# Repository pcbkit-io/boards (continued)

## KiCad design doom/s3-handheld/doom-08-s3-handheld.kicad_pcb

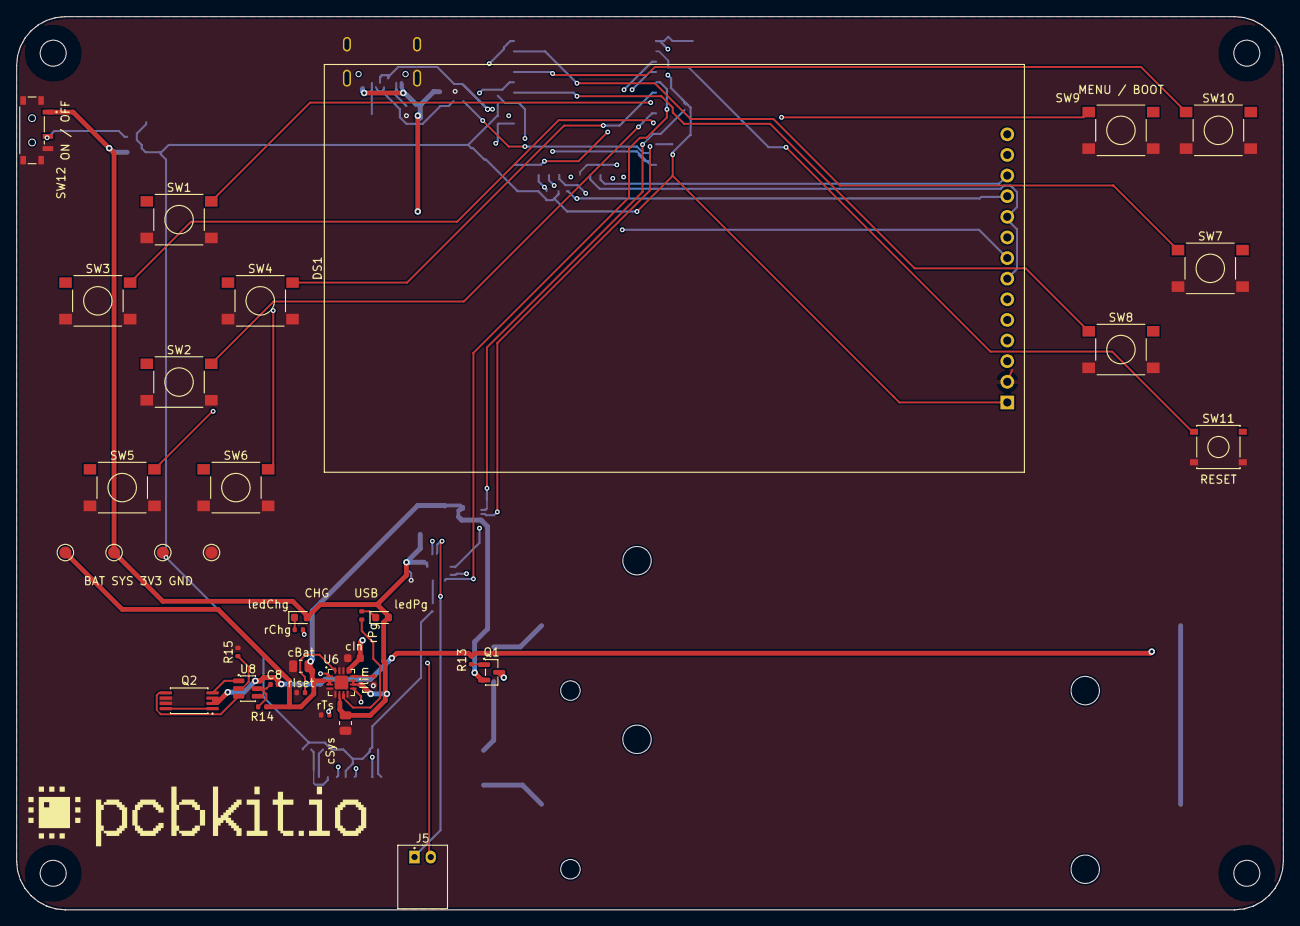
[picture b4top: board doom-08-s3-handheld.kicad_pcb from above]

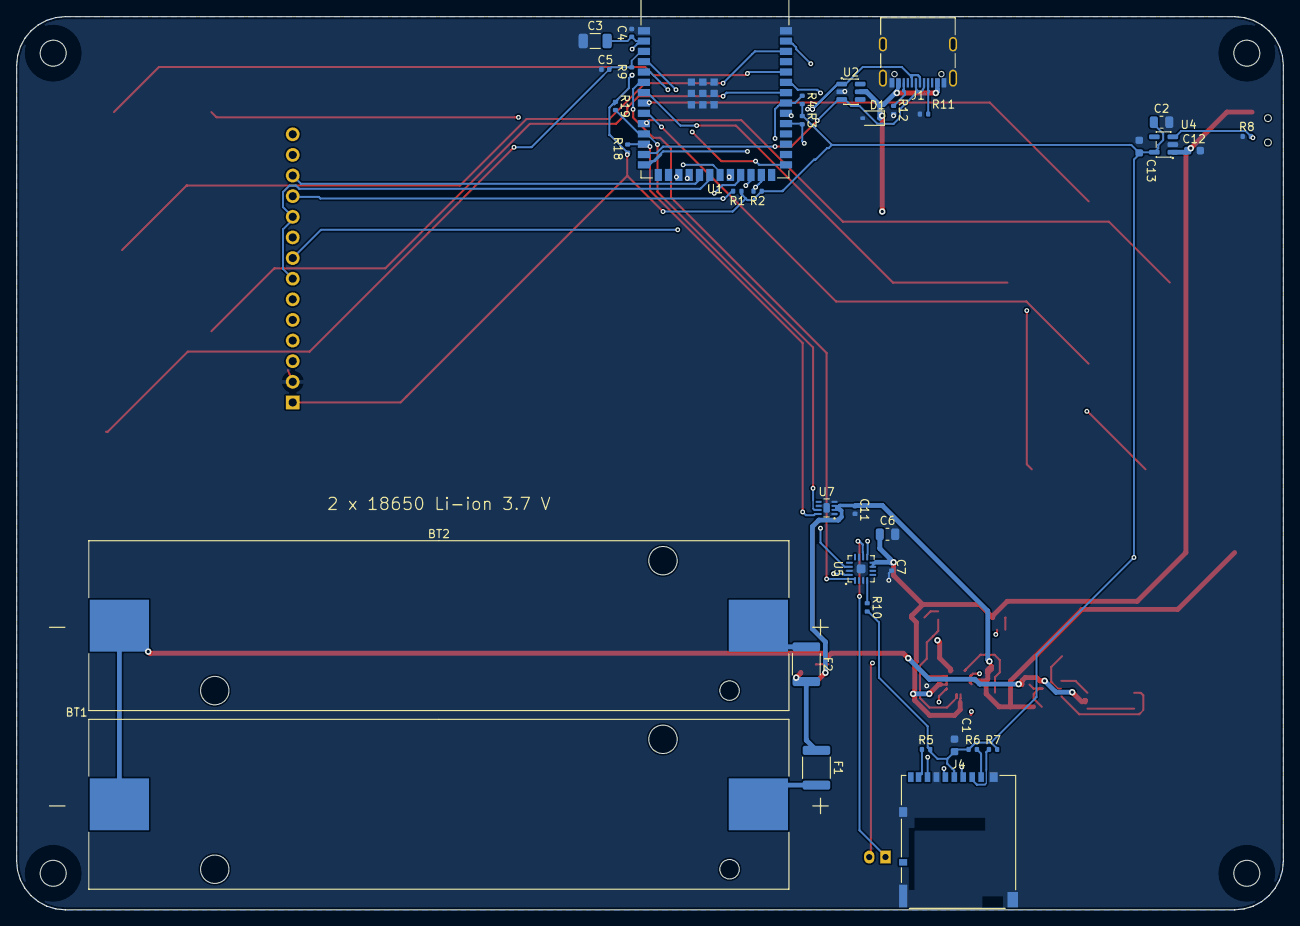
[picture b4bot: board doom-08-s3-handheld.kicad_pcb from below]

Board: 4 copper layers, 156.0 x 110.0 mm, 77 parts (36 on the bottom side), 61 nets.

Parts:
BT1, BT2: 1042; BatteryHolder_Keystone_1042_1x18650
C1: 10uF; C_0603_1608Metric
C2: 22uF; C_0805_2012Metric
C3: 22uF; C_1206_3216Metric
C4, C7, C8, C11: 100nF; C_0402_1005Metric
C5: 1uF; C_0402_1005Metric
C6: 10uF; C_0805_2012Metric
C12, C13: 1uF; C_0603_1608Metric
D1: tvs 5V; D_SOD-323
DS1: MSP2807 2.8in 240x320 SPI TFT module with touch (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; TFT_2.8in_ILI9341_Socket_1x14_P2.54mm
F1, F2: PTC 2000mA; Fuse_1812_4532Metric
H1, H2, H3, H4: MountingHole_3.2mm_M3
J1: USB4105-GF-A; USB_C_Receptacle_USB2.0_16P
J4: DM3AT-SF-PEJM5; Hirose_DM3AT_microSD_socket_push-push
J5: S2B-PH-K-S(LF)(SN); JST_PH_S2B-PH-K_1x02_P2.00mm_Horizontal
Q1: AO3401A; SOT-23
Q2: FS8205A; TSSOP-8_4.4x2.93mm_P0.65mm
R1, R2, R3, R4, R5, R6, R7, R9: 10kohm; R_0402_1005Metric
R8, R13: 100kohm; R_0402_1005Metric
R10: 634kohm; R_0402_1005Metric
R11, R12: 5.1kohm; R_0402_1005Metric
R14: 100ohm; R_0402_1005Metric
R15: 1kohm; R_0402_1005Metric
R18, R19: 3.3kohm; R_0402_1005Metric
SW1, SW2, SW3, SW4, SW5, SW6, SW7, SW8, SW9, SW10: PTS645SM43SMTR92 LFS; SW_Tactile_SPST_6x6mm_SMD
SW11: TS-1187A-B-A-B; SW_Tactile_SPST_5.1x5.1mm_SMD
SW12: MSK12C02; SW_Slide_SPDT_Shouhan_MSK12C02
U1: ESP32-S3-WROOM-1-N16R8; ESP32-S3-WROOM-1_module_18x25.5mm_40_edge_pads_EPAD
U2: USBLC6-2SC6; SOT-23-6
U4: TLV75733PDBVR; SOT-23-5
U5: MAX98357AETE+T; QFN-16-1EP_3x3mm_P0.5mm_EP1.1x1.1mm
U6: BQ24075RGTR; QFN-16-1EP_3x3mm_P0.5mm_EP1.68x1.68mm
U7: MAX17048G+T10; DFN-8-1EP_2x2mm_P0.5mm_EP0.8x1.2mm
U8: DW01A; SOT-6_1.6x2.9mm_P0.95mm
cBat: 4.7uF; C_0805_2012Metric
cIn: 1uF; C_0603_1608Metric
cSys: 4.7uF; C_0805_2012Metric
ledChg: red; LED_0603_1608Metric
ledPg: green; LED_0603_1608Metric
logo: Logo_PCBKit_pcbkit.io
rChg: 1.5kohm; R_0402_1005Metric
rIlim: 1.18kohm; R_0402_1005Metric
rIset: 1.13kohm; R_0402_1005Metric
rPg: 1.5kohm; R_0402_1005Metric
rTs: 10kohm; R_0402_1005Metric
tpBat: TestPoint_Round_D1.5mm
tpGnd: TestPoint_Round_D1.5mm
tpSys: TestPoint_Round_D1.5mm
tpV3: TestPoint_Round_D1.5mm

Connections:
BAT: C11.1 (a), Q1.2 (S), R14.1 (a), U6.2 (BAT), U6.3 (BAT), U7.2 (CELL), U7.3 (VDD), cBat.1 (a), tpBat.1
BAT_IN: F1.2 (b), F2.2 (b), Q1.3 (D)
CELL1_P: BT1.2 (C2), F1.1 (a)
CELL2_P: BT2.2 (C2), F2.1 (a)
CELL_N: BT1.1 (C1), BT2.1 (C1), C8.1 (a), Q2.2 (S1), Q2.3 (S1), R13.2 (b), U8.6 (GND)
CHG_LED: ledChg.1 (K), rChg.2 (b)
CHG_N: U6.9 (nCHG), rChg.1 (a)
DN: J1.A7 (DN), J1.B7 (DN), U1.13 (IO19), U2.3 (IO2)
DOWN: SW2.1 (a), U1.9 (IO16)
DP: J1.A6 (DP), J1.B6 (DP), U1.14 (IO20), U2.1 (IO1)
EN: C5.1 (a), R9.2 (b), SW11.1 (a), U1.3 (EN)
ENTER: SW10.1 (a), U1.36 (RXD0)
FIRE: SW7.1 (a), U1.38 (IO2)
GND: C1.2 (b), C2.2 (b), C3.2 (b), C4.2 (b), C5.2 (b), C6.2 (b), C7.2 (b), C11.2 (b), C12.2 (b), C13.2 (b), D1.2 (A), DS1.2 (GND), J1.A1 (GND), J1.A12, J1.B1 (GND), J1.B12, J1.S1 (SHIELD), J4.6 (VSS), J4.SH, Q2.6 (S2), Q2.7 (S2), R8.2 (b), R11.2 (b), R12.2 (b), R15.2 (b), SW1.2 (b), SW2.2 (b), SW3.2 (b), SW4.2 (b), SW5.2 (b), SW6.2 (b), SW7.2 (b), SW8.2 (b), SW9.2 (b), SW10.2 (b), SW11.2 (b), SW12.3 (B), SW12.4 (SHELL), U1.1 (GND), U1.40 (GND), U1.41 (GND), U2.2 (GND), U4.2 (GND), U5.3 (GND), U5.11 (GND), U5.15 (GND), U5.17 (EP), U6.4 (nCE), U6.5 (EN2), U6.8 (VSS), U6.14 (TMR), U6.15 (SYSOFF), U6.17 (VSS), U7.1 (CTG), U7.4 (GND), U7.6 (QSTRT), U7.9 (EP), cBat.2 (b), cIn.2 (b), cSys.2 (b), rIlim.2 (b), rIset.2 (b), rTs.2 (b), tpGnd.1
I2S_BCK: U1.4 (IO4), U5.16 (BCLK)
I2S_DIN: U1.6 (IO6), U5.1 (DIN)
I2S_LRCK: U1.5 (IO5), U5.14 (LRCLK)
ILIM: U6.12 (ILIM), rIlim.1 (a)
ISET: U6.16 (ISET), rIset.1 (a)
LCD_BL: DS1.8 (LED), U1.23 (IO21)
LCD_CS: DS1.3 (CS), U1.18 (IO10)
LCD_DC: DS1.5 (DC), U1.17 (IO9)
LCD_RST: DS1.4 (RESET), U1.22 (IO14)
LDO_EN: R8.1 (a), SW12.2 (COM), U4.3 (EN)
LEFT: SW3.1 (a), U1.10 (IO17)
MENU: SW9.1 (a), U1.27 (IO0)
MISO: DS1.9 (SDO), DS1.13 (T_DO), U1.21 (IO13)
MOSI: DS1.6 (SDI), DS1.12 (T_DIN), U1.19 (IO11)
unnamed: C8.2 (b), R14.2 (b), U8.5 (VCC)
unnamed: Q2.4 (G1), U8.1 (OD)
unnamed: Q2.5 (G2), U8.3 (OC)
unnamed: R10.2 (b), U5.4 (SD_MODE)
unnamed: R15.1 (a), U8.2 (CS)
PG_LED: ledPg.1 (K), rPg.2 (b)
PG_N: U6.7 (nPGOOD), rPg.1 (a)
RIGHT: SW4.1 (a), U1.7 (IO7)
SCK: DS1.7 (SCK), DS1.10 (T_CLK), U1.20 (IO12)
SCL: R19.2 (b), U1.11 (IO18), U7.7 (SCL)
SDA: R18.2 (b), U1.12 (IO8), U7.8 (SDA)
SD_CLK: J4.5 (CLK), U1.32 (IO39)
SD_CMD: J4.3 (CMD), R3.2 (b), U1.31 (IO38)
SD_D0: J4.7 (DAT0), R4.1 (a), U1.33 (IO40)
SD_D1: J4.8 (DAT1), R5.1 (a)
SD_D2: J4.1 (DAT2), R6.2 (b)
SD_D3: J4.2 (CD_DAT3), R7.1 (a)
SPK_N: J5.1 (C1), U5.10 (OUTN)
SPK_P: J5.2 (C2), U5.9 (OUTP)
STRAFE_L: SW5.1 (a), U1.35 (IO42)
STRAFE_R: SW6.1 (a), U1.39 (IO1)
SYS: C6.1 (a), C7.1 (a), C12.1 (a), SW12.1 (A), U4.1 (IN), U5.7 (VDD), U5.8 (VDD), U6.6 (EN1), U6.10 (OUT), U6.11 (OUT), cSys.1 (a), ledChg.2 (A), ledPg.2 (A), tpSys.1
TS: U6.1 (TS), rTs.1 (a)
T_CS: DS1.11 (T_CS), R1.2 (b), U1.24 (IO47)
T_IRQ: DS1.14 (T_IRQ), R2.2 (b), U1.25 (IO48)
U8Support/DRAIN: Q2.1 (D12), Q2.8 (D12)
UP: SW1.1 (a), U1.8 (IO15)
USE: SW8.1 (a), U1.34 (IO41)
V3: C1.1 (a), C2.1 (a), C3.1 (a), C4.1 (a), C13.1 (a), DS1.1 (VCC), J4.4 (VDD), R1.1 (a), R2.1 (a), R3.1 (a), R4.2 (b), R5.2 (b), R6.1 (a), R7.2 (b), R9.1 (a), R10.1 (a), R18.1 (a), R19.1 (a), U1.2 (P3V3), U4.5 (OUT), tpV3.1
VBUS: D1.1 (K), J1.A4 (VBUS), J1.A9, J1.B4 (VBUS), J1.B9, U2.5 (VBUS), U6.13 (IN), cIn.1 (a)
reversed/gate: Q1.1 (G), R13.1 (a)
usb/power/cc1: J1.A5 (CC1), R11.1 (a)
usb/power/cc2: J1.B5 (CC2), R12.1 (a)

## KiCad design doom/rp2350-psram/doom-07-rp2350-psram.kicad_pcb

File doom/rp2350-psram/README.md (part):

# 07 · rp2350-psram — the bare RP2350A with QSPI flash and PSRAM on one bus

The reference device's chip without the module: an RP2350A with Raspberry Pi's minimal design
(core switching regulator, 12 MHz crystal), a 16 MB W25Q128 on QSPI chip select 0 and an 8 MB
APS6404L PSRAM on the QMI's chip select 1 (GPIO8) sharing the same SCLK and SD0–SD3, so both are
memory-mapped through the XIP cache and Doom runs as an ordinary program. Two 18650 Li-ion cells
power it, behind reverse-cell and DW01A protection, charged from the USB-C by a BQ24075 with power
path, with a MAX17048 fuel gauge and a switched LDO. JLCPCB assembles everything but the display
module, which plugs into the socket it solders.

| | |
|---|---|
| Processor | RP2350A (QFN-60): 2 × **Cortex-M33** (ARMv8-M Mainline, FPU, DSP, TrustZone) **or** 2 × **Hazard3** RISC-V (RV32IMAC + Zba/Zbb/Zbs/Zbkb/Zcb/Zcmp), the architecture chosen by the image; 150 MHz; 520 KB SRAM; on-chip 1.1 V switching regulator (3.3 µH) |
| Memory | W25Q128JVSIQ 16 MB on QSPI_SS (CS0); APS6404L-3SQR 8 MB PSRAM on GPIO8 = QMI CS1 (XIP_CS1n); both mapped by the QMI (flash at 0x1000_0000, PSRAM at 0x1100_0000), 16 KB XIP cache |
| Display | 2.0" 240 × 320 IPS, ST7789 (MSP2008), SPI0 (GPIO18 SCK, GPIO19 MOSI, GPIO17 CS, GPIO16 DC, GPIO20 RES, GPIO21 backlight); landscape 320 × 240 |
| Storage | microSD on SPI1 (GPIO10–13), card detect GPIO14 |
| Input | 10 × 6 mm tact switches: GPIO0–5 (d-pad, fire, use), GPIO9, GPIO15 (strafe), GPIO25 (menu), GPIO26 (enter) |
| Sound | PIO I2S (GPIO22 BCK, GPIO23 LRCK, GPIO24 DIN) → MAX98357A → 8 Ω speaker |
| Power | 2 × 18650 Li-ion in parallel (1S2P, a 2 A resettable fuse per cell) → reverse-cell P-FET (AO3401A) → DW01A + FS8205A; USB-C (1 A PTC + TVS) → **BQ24075** (power path SYS; USB500 mode, 800 mA charge) → TLV75533 (EN on the slide switch) → 3.3 V; **MAX17048** gauge on the pack, on I2C1 (GPIO6 SDA, GPIO7 SCL, 0x36, alert GPIO29); amplifier on SYS |
| Programming | USB-C to the RP2350's USB (27 Ω, USBLC6 ESD array): hold BOOT (1 kΩ on QSPI_SS), tap RESET → the boot ROM's UF2 drive, for ARM or RISC-V images; SWD + RUN on a 4-pin header on the back |
| Board | 144 × 110 mm, **4 layers** (In1 a solid GND plane), four M3 holes; front: display, buttons, BOOT, RESET, on/off switch, USB-C, charge LEDs, test pads; back: the RP2350 and the rest, the two 18650 holders across the top half. Net classes: 0.15 mm tracks and gaps with 0.45 / 0.2 mm vias by default (the QFN-60's 0.4 mm pitch), 0.3 mm for 3.3 V and the core, 0.6 mm with 0.8 / 0.4 mm vias for the power paths |

<!-- STATUS -->
**Board status** (measured on the dev host with PCBKit's CLI): `pcbkit check`: complete — 0 errors, 4 warnings (diff-pair-uncoupled, erc-rail-name, track-width-class), 0 unrouted nets. 102 components, 77 nets, 1183 track segments (3262 mm), 167 vias.
`analysis.run { lens: "ready" }`: Typical scenario, partly by family estimates. Nothing to fix, 5 to consider, 17 ok: weigh the warnings (tell the person about the ones that are their choice), then the board is ready to order.
`pcbkit export --format fab` succeeds without `--force`: every assembled line of the BOM has an LCSC code.

| Warning | Why it stays |
|---|---|
| `diff-pair-uncoupled`, `skew` (DP / DN, ~60 mm) | USB full speed (12 Mbit/s): the connector is on the front edge, the RP2350 on the back; tens of mm uncoupled and ten of skew (~70 ps) are harmless against 4–20 ns edges |
| `track-width-class` (DP necked to 0.15 mm) | a short neck at the 0.4 mm pitch pads; a signal |
| ready lens: J3 is not on an edge | the SWD header is for a debug probe's jumper wires, not a cable to the outside |
| ready lens: thermal parameters, typical scenario | estimates of the analysis, not faults of the board |
<!-- /STATUS -->

## Run it in the browser

Open https://app.pcbkit.io/github/pcbkit-io/boards/tree/main/doom/rp2350-psram, open the
Laboratory and press **Run**: the page builds `doom/` for the RP2350 (with `DOOM1.WAD` linked into
flash), boots the image on a register-level model of the chip and its PSRAM, and draws the
display's frames on the board. Play with the keyboard (arrows, F fire, Space use, comma/period
strafe, M menu, Enter) or a gamepad (`input.js` maps a standard controller).

## Why it runs Doom

This is the reference device's software on its own board: Doom with its zone heap and screens in
the PSRAM, the shareware WAD linked into the flash, on one Hazard3 core at 150 MHz; each 320 × 200
frame goes to the display as RGB565 over SPI0 at 25 MHz. Not measured on hardware: the simulation
runs one instruction per clock and charges no flash or PSRAM latency.

## Power

Two 18650 Li-ion cells in Keystone 1042 holders on the back, in parallel (1S2P, 3.0–4.2 V, about
5–7 Ah together), as on `rp2350-handheld`:

- **Reverse cells:** an AO3401A P-MOSFET in the plus line, its gate at the cells' minus: cells put
  in backwards leave it off and the board unpowered (it conducts both ways when they are right, so
  charging goes through it too). One cell reversed against the other is what the **per-cell fuses**
  are for: each holder's + reaches the pack through its own 2 A resettable fuse (Littelfuse
  1812L200/16GR: 16 V, 100 A interrupting), so a cell put in backwards, or one much fuller than
  the other, trips both in milliseconds instead of shorting the two cells together (tens of
  amperes); take the cell out and they reset. Still put each cell's + at the end the silkscreen
  marks.
- **Protection:** DW01A + FS8205A in the pack's minus: over-charge 4.3 V, over-discharge 2.4 V,
  over-current about 3 A and short circuit, for the pack. Flat-top unprotected 18650 cells fit
  the holders.
- **Charger with power path:** a TI BQ24075 (the BQ24074's sibling with SYSOFF and a fixed
  current-based termination) from the USB-C VBUS (through a 1 A PTC fuse, a 5 V TVS after it), in
  USB500 mode (at most 500 mA from the port; 5.1 kΩ on CC), 800 mA fast charge (RISET 1.13 kΩ),
  input limit RILIM 1.18 kΩ, safety timers off (two cells charge longer than its longest timer),
  TS tied to 10 kΩ (no thermistor). Its output SYS runs the board from USB when one is plugged in
  (flat or missing cells included) and from the cells otherwise.
- **Fuel gauge:** the MAX17048 measures the pack after the protection (its ModelGauge needs no
  sense resistor; two cells in parallel read as one cell of twice the capacity).
- **Rails:** SYS feeds the TLV75533 LDO (3.3 V; it follows the cells below about 3.55 V) and the
  MAX98357A directly; the slide switch on the left edge enables the LDO (100 kΩ holds it off), the
  amplifier is shut down by its SD_MODE while the RP2350 is off. The cells keep charging with the
  switch off.

| State | Current (estimate) |
|---|---|
| RP2350 at 150 MHz + PSRAM + flash | ~45 mA at 3.3 V |
| ST7789 2.0" with backlight | ~40 mA |
| MAX98357A | 20–200 mA from SYS |
| **Typical** | **~120 mA at 3.7 V** |

Two 3000 mAh cells → **about 50 h** of play (estimate). A full charge of two empty cells at 800 mA
takes about 8 h (longer from a 500 mA USB 2.0 port).

## Charging

Plug a USB-C charger or computer into the USB-C on the bottom edge. The red LED (CHG) is on while
the cells charge and goes out when they are full; the green LED (USB) is on while USB power is
present. The board runs from USB while it charges, switched on or off. Insert both cells with +
at the end the back's silkscreen marks.

## Flashing on arrival

Nothing to solder and no programmer: the RP2350's boot ROM has a USB loader.

1. Connect the USB-C to a computer.
2. Hold **BOOT**, tap **RESET**, release BOOT (or hold BOOT while plugging in): the board appears
   as the **RP2350** drive.
3. Copy `U1.uf2` onto it (the boot ROM runs Arm or RISC-V images); or
   `picotool load -x U1.uf2` with the board in BOOTSEL.

Or over SWD: the 4-pin header on the back (SWCLK, GND, SWDIO, RUN) takes a Raspberry Pi Debug
Probe. The game data goes in the flash with the program.

## Modules plugged in by hand

- **DS1: 2.0" 240 × 320 ST7789 IPS SPI module** (MSP2008 pinout, 8 pins: GND, VCC, SCL, SDA, RES,
  DC, CS, BLK) into the 1x8 socket JLCPCB solders on the front.
- An **8 Ω speaker** (up to 3 W) with a JST PH 2-pin plug into J5 at the right edge of the back.
- Two **18650 cells**.

## Firmware: build

- `doom/` is the program: `doom_rp2350.c` is the platform layer (clocks from the 12 MHz crystal,
  the PSRAM on QMI chip select 1 = GPIO8, which the firmware sets up — the boot ROM only sets up
  CS0 — the display, the buttons, the timer), the engine is sysprog21/doom_riscv, unchanged. Pins:
  display SCK GPIO18, MOSI GPIO19, CS GPIO17, D/C GPIO16, RESET GPIO20, backlight GPIO21; buttons
  up GPIO0, down 1, left 2, right 3, fire 4, use 5, strafe left 9, strafe right 15, menu 25,
  enter 26. The ST7789's IPS panel needs inversion on (INVON) for true colours. Not used yet: the
  microSD card, the amplifier, the fuel gauge; no console (GPIO0 and GPIO1 are buttons).
- **Build:** in PCBKit, the Laboratory's **Run** builds it (RISC-V, `DOOM1.WAD` linked into flash);
  then export the firmware (`export.run { format: "firmware" }`, or the app's export menu): `U1.uf2`.

## Bill of materials

Rough cost at 10 pieces (estimates): RP2350A $1.10 · W25Q128 $1.00 · APS6404L $1.20 · crystal $0.15 ·
3.3 µH inductor $0.20 · ST7789 2.0" $4.00 · microSD socket $0.60 · MAX98357A $0.90 · BQ24075 $1.10 ·
DW01A + FS8205A + AO3401A $0.25 · MAX17048 $1.60 · TLV75533 $0.20 · USB-C + ESD + TVS + PTC $0.50 ·
buttons $3.50 · passives $2.00 · two 18650 holders $9.80 · 4-layer PCB $4.00 · speaker $1.00 →
**about $37** without the cells, plus assembly.

<!-- BOM -->
The assembly BOM as `pcbkit export --format fab` writes it (JLCPCB assembly: LCSC codes; the modules' lines are their sockets):

| Qty | Refs | Part | LCSC | Footprint |
|---|---|---|---|---|
| 2 | BT1, BT2 | 1042 | C5249310 | BatteryHolder_Keystone_1042_1x18650 |
| 1 | C1 | 10uF | C19702 | C_0603_1608Metric |
| 2 | C2, C3 | 15pF | C1548 | C_0402_1005Metric |
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
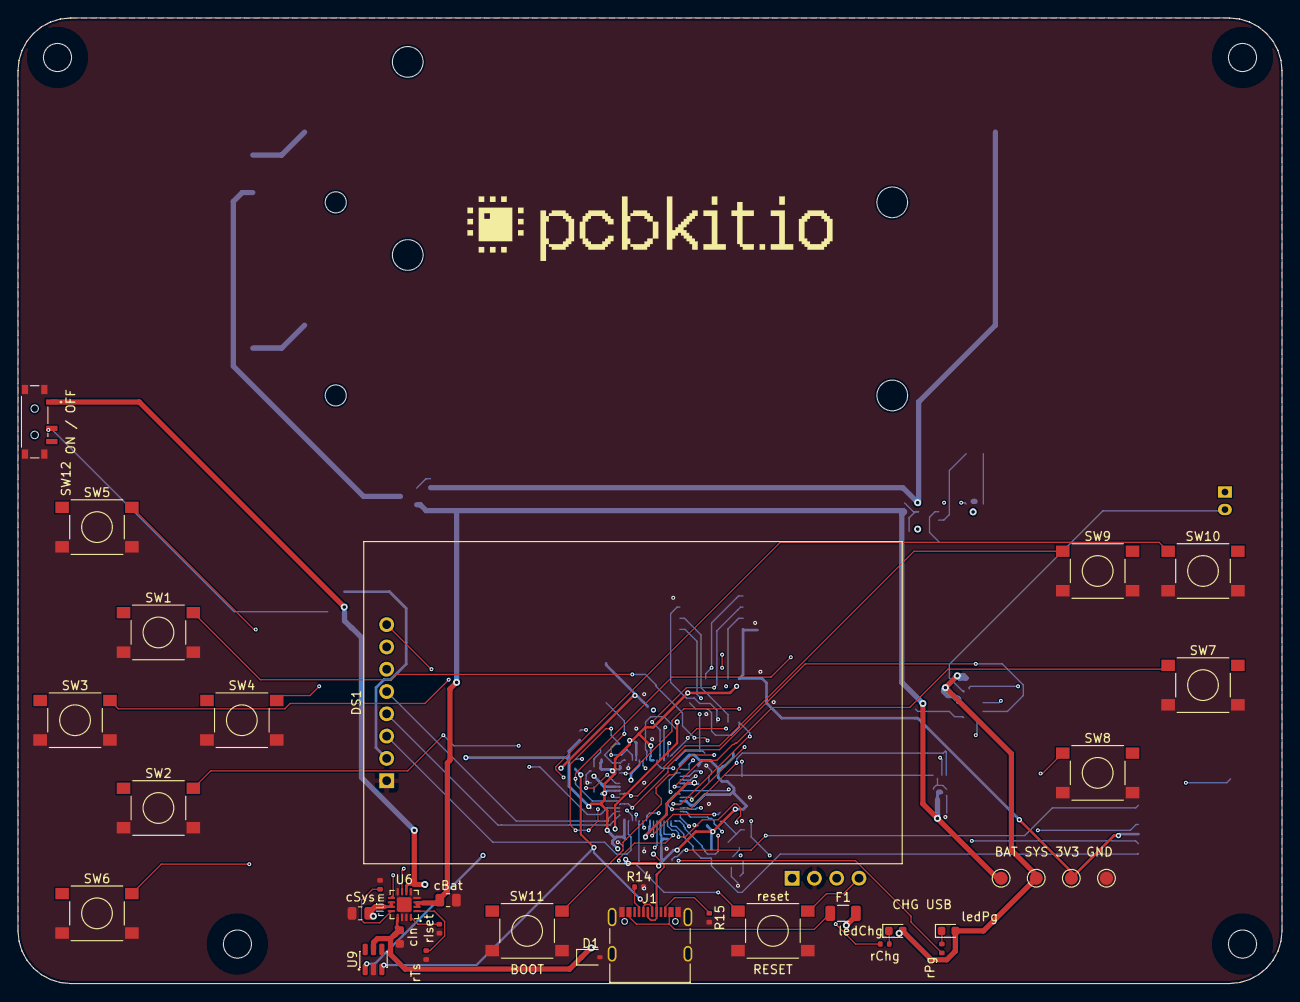
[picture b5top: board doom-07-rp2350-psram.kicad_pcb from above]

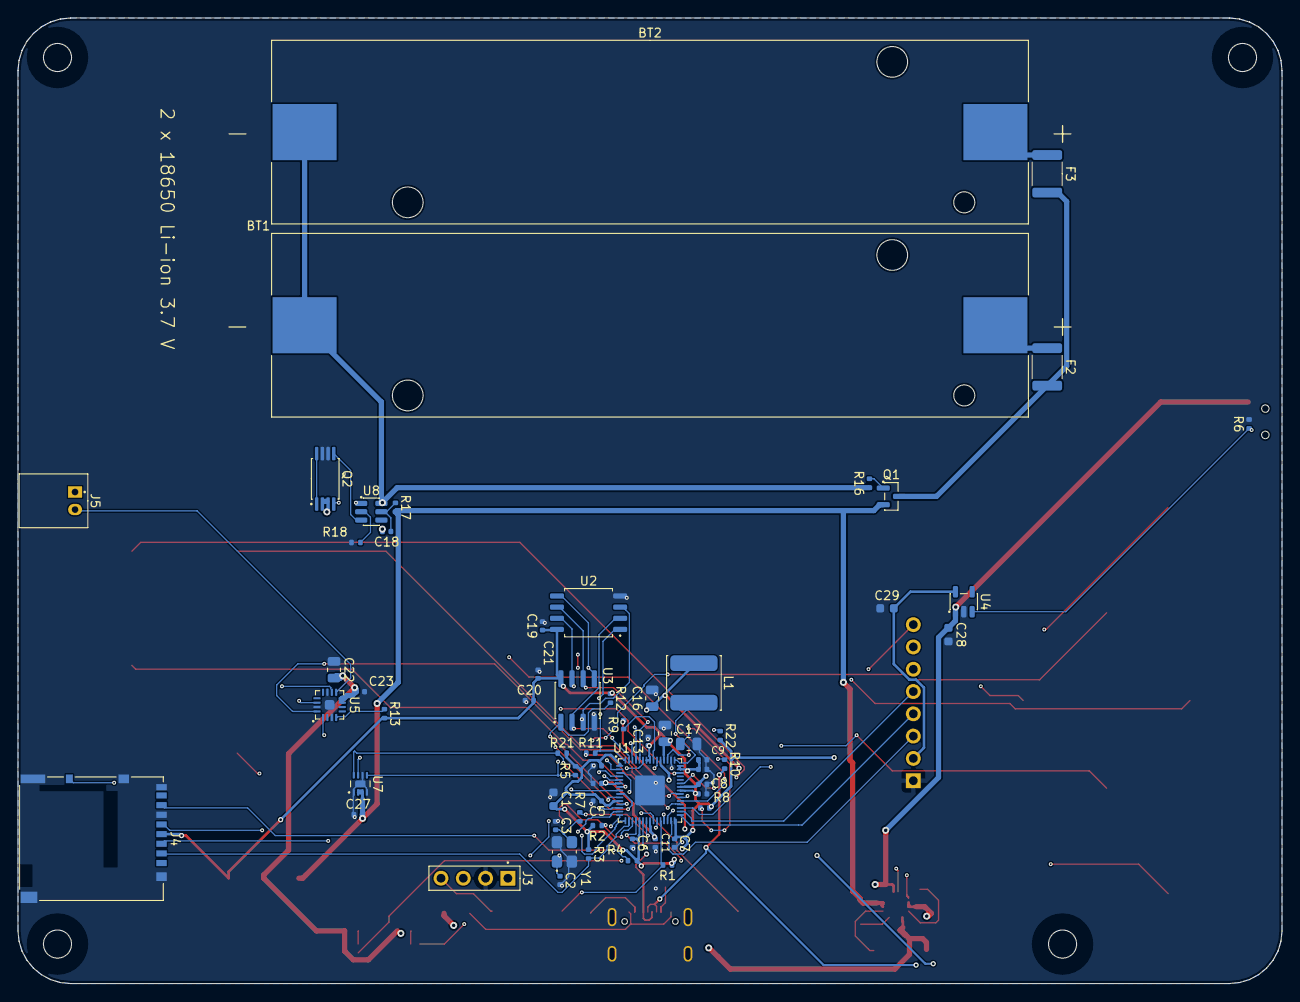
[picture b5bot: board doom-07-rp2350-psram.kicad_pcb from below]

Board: 4 copper layers, 144.0 x 110.0 mm, 102 parts (62 on the bottom side), 77 nets.

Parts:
BT1, BT2: 1042; BatteryHolder_Keystone_1042_1x18650
C1: 10uF; C_0603_1608Metric
C2, C3: 15pF; C_0402_1005Metric
C4, C5, C6, C7, C8, C9, C10, C11, C12, C13, C14, C18, C19, C21, C23, C27: 100nF; C_0402_1005Metric
C15, C16, C17: 4.7uF; C_0805_2012Metric
C20: 1uF; C_0402_1005Metric
C22: 10uF; C_0805_2012Metric
C28, C29: 1uF; C_0603_1608Metric
D1: tvs 5V; D_SOD-323
DS1: MSP2008 2.0in 240x320 IPS SPI module (ST7789); TFT_2.0in_ST7789_Socket_1x08_P2.54mm
F1: PTC 750mA; Fuse_1206_3216Metric
F2, F3: PTC 2000mA; Fuse_1812_4532Metric
H1, H2, H3, H4: MountingHole_3.2mm_M3
J1: USB4105-GF-A; USB_C_Receptacle_USB2.0_16P
J3: PinHeader_1x04_P2.54mm_Vertical
J4: DM3AT-SF-PEJM5; Hirose_DM3AT_microSD_socket_push-push
J5: S2B-PH-K-S(LF)(SN); JST_PH_S2B-PH-K_1x02_P2.00mm_Horizontal
L1: 3.3uH; L_Power_6x6mm
Q1: AO3401A; SOT-23
Q2: FS8205A; TSSOP-8_4.4x2.93mm_P0.65mm
R1, R2, R3, R4, R5, R12: 10kohm; R_0402_1005Metric
R6, R16: 100kohm; R_0402_1005Metric
R7, R11, R18: 1kohm; R_0402_1005Metric
R8: 33ohm; R_0402_1005Metric
R9, R10: 27ohm; R_0402_1005Metric
R13: 634kohm; R_0402_1005Metric
R14, R15: 5.1kohm; R_0402_1005Metric
R17: 100ohm; R_0402_1005Metric
R21, R22: 3.3kohm; R_0402_1005Metric
SW1, SW2, SW3, SW4, SW5, SW6, SW7, SW8, SW9, SW10, SW11: PTS645SM43SMTR92 LFS; SW_Tactile_SPST_6x6mm_SMD
SW12: MSK12C02; SW_Slide_SPDT_Shouhan_MSK12C02
U1: RP2350A; QFN-60-1EP_7x7mm_P0.4mm_EP3.4x3.4mm
U2: W25Q128JVSIQ; SOIC-8_5.23x5.28mm_P1.27mm
U3: APS6404L-3SQR-SN; SOIC-8_3.9x4.9mm_P1.27mm
U4: TLV75533PDBVR; SOT-23-5
U5: MAX98357AETE+T; QFN-16-1EP_3x3mm_P0.5mm_EP1.1x1.1mm
U6: BQ24075RGTR; QFN-16-1EP_3x3mm_P0.5mm_EP1.68x1.68mm
U7: MAX17048G+T10; DFN-8-1EP_2x2mm_P0.5mm_EP0.8x1.2mm
U8: DW01A; SOT-6_1.6x2.9mm_P0.95mm
U9: USBLC6-2SC6; SOT-23-6
Y1: 12MHz 10pF; Crystal_SMD_3225-4Pin
cBat: 4.7uF; C_0805_2012Metric
cIn: 1uF; C_0603_1608Metric
cSys: 4.7uF; C_0805_2012Metric
ledChg: red; LED_0603_1608Metric
ledPg: green; LED_0603_1608Metric
logo: Logo_PCBKit_pcbkit.io
rChg: 1.5kohm; R_0402_1005Metric
rIlim: 1.18kohm; R_0402_1005Metric
rIset: 1.13kohm; R_0402_1005Metric
rPg: 1.5kohm; R_0402_1005Metric
rTs: 10kohm; R_0402_1005Metric
reset: PTS645SM43SMTR92 LFS; SW_Tactile_SPST_6x6mm_SMD
tpBat: TestPoint_Round_D1.5mm
tpGnd: TestPoint_Round_D1.5mm
tpSys: TestPoint_Round_D1.5mm
tpV3: TestPoint_Round_D1.5mm

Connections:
BAT: C27.1 (a), Q1.2 (S), R17.2 (b), U6.2 (BAT), U6.3 (BAT), U7.2 (CELL), U7.3 (VDD), cBat.1 (a), tpBat.1
BAT_IN: F2.2 (b), F3.2 (b), Q1.3 (D)
BOOTSEL: R11.1 (a), SW11.1 (a)
CELL1_P: BT1.2 (C2), F2.1 (a)
CELL2_P: BT2.2 (C2), F3.1 (a)
CELL_N: BT1.1 (C1), BT2.1 (C1), C18.2 (b), Q2.2 (S1), Q2.3 (S1), R16.1 (a), U8.6 (GND)
CHG_LED: ledChg.1 (K), rChg.1 (a)
CHG_N: U6.9 (nCHG), rChg.2 (b)
DN: J1.A7 (DN), J1.B7 (DN), R10.2 (b), U9.3 (IO2)
DOWN: SW2.1 (a), U1.3 (GPIO1)
DP: J1.A6 (DP), J1.B6 (DP), R9.2 (b), U9.1 (IO1)
ENTER: SW10.1 (a), U1.40 (GPIO26_ADC0)
FIRE: SW7.1 (a), U1.7 (GPIO4)
FUEL_ALRT: R5.1 (a), U1.43 (GPIO29_ADC3), U7.5 (ALRT)
GND: C1.2 (b), C2.2 (b), C3.2 (b), C4.2 (b), C5.2 (b), C6.2 (b), C7.2 (b), C8.2 (b), C9.2 (b), C10.2 (b), C11.2 (b), C12.2 (b), C13.2 (b), C14.2 (b), C15.2 (b), C16.2 (b), C17.2 (b), C19.2 (b), C20.2 (b), C21.2 (b), C22.2 (b), C23.2 (b), C27.2 (b), C28.2 (b), C29.2 (b), D1.2 (A), DS1.1 (GND), J1.A1 (GND), J1.A12, J1.B1 (GND), J1.B12, J1.S1 (SHIELD), J3.2, J4.6 (VSS), J4.10 (CD_B), J4.SH, Q2.6 (S2), Q2.7 (S2), R6.2 (b), R14.2 (b), R15.2 (b), R18.2 (b), SW1.2 (b), SW2.2 (b), SW3.2 (b), SW4.2 (b), SW5.2 (b), SW6.2 (b), SW7.2 (b), SW8.2 (b), SW9.2 (b), SW10.2 (b), SW11.2 (b), SW12.4 (SHELL), U1.47 (VREG_PGND), U1.61 (GND), U2.4 (GND), U3.4 (VSS), U4.2 (GND), U5.3 (GND), U5.11 (GND), U5.15 (GND), U5.17 (EP), U6.4 (nCE), U6.5 (EN2), U6.8 (VSS), U6.14 (TMR), U6.15 (SYSOFF), U6.17 (VSS), U7.1 (CTG), U7.4 (GND), U7.6 (QSTRT), U7.9 (EP), U9.2 (GND), Y1.2 (GND), Y1.4 (GND), cBat.2 (b), cIn.2 (b), cSys.2 (b), rIlim.2 (b), rIset.2 (b), rTs.2 (b), reset.2 (b), tpGnd.1
I2S_BCK: U1.34 (GPIO22), U5.16 (BCLK)
I2S_DIN: U1.36 (GPIO24), U5.1 (DIN)
I2S_LRCK: U1.35 (GPIO23), U5.14 (LRCLK)
ILIM: U6.12 (ILIM), rIlim.1 (a)
ISET: U6.16 (ISET), rIset.1 (a)
LCD_BL: DS1.8 (BLK), U1.33 (GPIO21)
LCD_CS: DS1.7 (CS), U1.28 (GPIO17)
LCD_DC: DS1.6 (DC), U1.27 (GPIO16)
LCD_RST: DS1.5 (RES), U1.32 (GPIO20)
LDO_EN: R6.1 (a), SW12.2 (COM), U4.3 (EN)
LEFT: SW3.1 (a), U1.4 (GPIO2)
MENU: SW9.1 (a), U1.37 (GPIO25)
MOSI: DS1.4 (SDA), U1.31 (GPIO19)
unnamed: C2.1 (a), U1.21 (XIN), Y1.1 (X1)
unnamed: C17.1 (a), R8.2 (b), U1.46 (VREG_AVDD)
unnamed: C18.1 (a), R17.1 (a), U8.5 (VCC)
unnamed: L1.2 (b), U1.48 (VREG_LX)
unnamed: Q2.4 (G1), U8.1 (OD)
unnamed: Q2.5 (G2), U8.3 (OC)
unnamed: R7.2 (b), U1.22 (XOUT)
unnamed: R9.1 (a), U1.52 (USB_DP)
unnamed: R10.1 (a), U1.51 (USB_DM)
unnamed: R13.1 (a), U5.4 (SD_MODE)
unnamed: R18.1 (a), U8.2 (CS)
PG_LED: ledPg.1 (K), rPg.1 (a)
PG_N: U6.7 (nPGOOD), rPg.2 (b)
PSRAM_CS: R12.2 (b), U1.12 (GPIO8), U3.1 (CE)
QSPI_SCLK: U1.56 (QSPI_SCLK), U2.6 (CLK), U3.6 (SCLK)
QSPI_SD0: U1.57 (QSPI_SD0), U2.5 (DI), U3.5 (SIO0)
QSPI_SD1: U1.59 (QSPI_SD1), U2.2 (DO), U3.2 (SIO1)
QSPI_SD2: U1.58 (QSPI_SD2), U2.3 (nWP), U3.3 (SIO2)
QSPI_SD3: U1.55 (QSPI_SD3), U2.7 (nHOLD), U3.7 (SIO3)
QSPI_SS: R11.2 (b), U1.60 (QSPI_SS), U2.1 (nCS)
RIGHT: SW4.1 (a), U1.5 (GPIO3)
RUN: J3.4, R1.2 (b), U1.26 (RUN), reset.1 (a)
SCK: DS1.3 (SCL), U1.29 (GPIO18)
SCL: R22.1 (a), U1.10 (GPIO7), U7.7 (SCL)
SDA: R21.1 (a), U1.9 (GPIO6), U7.8 (SDA)
SD_CD: J4.9 (CD_A), R2.1 (a), U1.18 (GPIO14)
SD_CS: J4.2 (CD_DAT3), R3.2 (b), U1.17 (GPIO13)
SD_MISO: J4.7 (DAT0), R4.2 (b), U1.16 (GPIO12)
SD_MOSI: J4.3 (CMD), U1.15 (GPIO11)
SD_SCK: J4.5 (CLK), U1.14 (GPIO10)
SPK_N: J5.1 (C1), U5.10 (OUTN)
SPK_P: J5.2 (C2), U5.9 (OUTP)
STRAFE_L: SW5.1 (a), U1.13 (GPIO9)
STRAFE_R: SW6.1 (a), U1.19 (GPIO15)
SWCLK: J3.1, U1.24 (SWCLK)
SWDIO: J3.3, U1.25 (SWDIO)
SYS: C22.1 (a), C23.1 (a), C28.1 (a), SW12.1 (A), U4.1 (IN), U5.7 (VDD), U5.8 (VDD), U6.6 (EN1), U6.10 (OUT), U6.11 (OUT), cSys.1 (a), ledChg.2 (A), ledPg.2 (A), tpSys.1
TS: U6.1 (TS), rTs.1 (a)
U1Support/XO: C3.1 (a), R7.1 (a), Y1.3 (X2)
U8Support/DRAIN: Q2.1 (D12), Q2.8 (D12)
UP: SW1.1 (a), U1.2 (GPIO0)
USE: SW8.1 (a), U1.8 (GPIO5)
V1V1: C10.1 (a), C11.1 (a), C12.1 (a), C16.1 (a), L1.1 (a), U1.6 (DVDD), U1.23 (DVDD), U1.39 (DVDD), U1.50 (VREG_FB)
V3: C1.1 (a), C4.1 (a), C5.1 (a), C6.1 (a), C7.1 (a), C8.1 (a), C9.1 (a), C13.1 (a), C14.1 (a), C15.1 (a), C19.1 (a), C20.1 (a), C21.1 (a), C29.1 (a), DS1.2 (VCC), J4.4 (VDD), R1.1 (a), R2.2 (b), R3.1 (a), R4.1 (a), R5.2 (b), R8.1 (a), R12.1 (a), R13.2 (b), R21.2 (b), R22.2 (b), U1.1 (IOVDD), U1.11 (IOVDD), U1.20 (IOVDD), U1.30 (IOVDD), U1.38 (IOVDD), U1.44 (ADC_AVDD), U1.45 (IOVDD), U1.49 (VREG_VIN), U1.53 (USB_OTP_VDD), U1.54 (QSPI_IOVDD), U2.8 (VCC), U3.8 (VDD), U4.5 (OUT), tpV3.1
VBUS: D1.1 (K), F1.2 (b), U6.13 (IN), U9.5 (VBUS), cIn.1 (a)
reversed/gate: Q1.1 (G), R16.2 (b)
usb/power/cc1: J1.A5 (CC1), R14.1 (a)
usb/power/cc2: J1.B5 (CC2), R15.1 (a)
usb/power/vbusIn: F1.1 (a), J1.A4 (VBUS), J1.A9, J1.B4 (VBUS), J1.B9

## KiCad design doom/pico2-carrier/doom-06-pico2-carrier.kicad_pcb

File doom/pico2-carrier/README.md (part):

# 06 · pico2-carrier — the reference device as an orderable carrier

PCBKit's reference Doom device, made orderable: a carrier for the **Pimoroni Pico Plus 2**
(RP2350B, 16 MB flash, **8 MB PSRAM** on QMI chip select 1 = GPIO47; the full game's data and heap
need both, a plain Pico 2 has neither room) on the Pico's 2 × 20 sockets — with
the same 2.8" ILI9341 touch TFT (MSP2807) and ten buttons as the reference, plus a PCM5102A DAC and a
headphone jack. It runs from two 18650 Li-ion cells on its back, charged from the module's USB.
JLCPCB assembles everything but the two modules, which plug into the sockets it solders.

| | |
|---|---|
| Processor | RP2350B on the Pico Plus 2: 2 × **Cortex-M33** (ARMv8-M Mainline, DSP, single-precision FPU, TrustZone) **or** 2 × **Hazard3** (RV32IMAC + Zba/Zbb/Zbs/Zbkb/Zcb/Zcmp), chosen by the image; 150 MHz; 520 KB SRAM; 16 MB QSPI flash and 8 MB PSRAM through the QMI's 16 KB XIP cache |
| Display | 2.8" 240 × 320 ILI9341 with XPT2046 resistive touch on SPI0 (GP18 SCK, GP19 MOSI, GP16 MISO, GP17 CS, GP20 DC, GP21 RESET, GP22 backlight; touch CS GP13, IRQ GP14) |
| Input | 10 × 6 mm tact switches, as the reference: d-pad GP0–GP3, fire GP4, use GP5, strafe L/R GP6/GP7, menu GP8, enter GP9 |
| Sound | PIO I2S (GP10 BCK, GP11 LRCK, GP12 DIN) → PCM5102A (hardware mode, PLL from BCK, mute on GP15) → 470 Ω / 2.2 nF → 3.5 mm stereo jack |
| Power | 2 × 18650 Li-ion in parallel (1S2P, a 2 A resettable fuse per cell, 3.0–4.2 V) behind reverse-cell (AO3401A) and DW01A + FS8205A protection; BQ24075 charger with power path from the module's USB; SYS → 1N5819HW → module VSYS; the module's buck-boost makes 3.3 V (up to 300 mA for the carrier) |
| Programming | the module's USB: BOOTSEL + plug → UF2 (RP2350's ROM accepts ARM and RISC-V images); SWD on the module's debug pads; the same port charges |
| Board | 160 × 100 mm, 2 layers, four M3 holes; front: display, ten buttons, charger, on/off switch, test pads; back: module (USB at the top edge), two 18650 holders, DAC, jack (right edge) |

<!-- STATUS -->
**Board status** (measured on the dev host with PCBKit's CLI): `pcbkit check`: complete — 0 errors, 4 warnings (erc-rail-name), 0 unrouted nets. 64 components, 55 nets, 513 track segments (2894 mm), 52 vias.
`analysis.run { lens: "ready" }`: Typical scenario, partly by family estimates. Nothing to fix, 2 to consider, 12 ok: weigh the warnings (tell the person about the ones that are their choice), then the board is ready to order.
`pcbkit export --format fab` succeeds without `--force`: every assembled line of the BOM has an LCSC code.
<!-- /STATUS -->

The ready lens's two notes are not faults: it estimates heat with generic package limits where the
modules' makers publish no thermal data, and reads the module's draw from its family (the board
dissipates well under 1 W). Keystone 1042 holders (C5249310) are stocked in hundreds at JLCPCB:
check before ordering more than a few boards.

## Run it in the browser

Open https://app.pcbkit.io/github/pcbkit-io/boards/tree/main/doom/pico2-carrier, open the
Laboratory and press **Run**: the page builds `doom/` for the RP2350 (with `DOOM1.WAD` linked into
flash), boots the image on a register-level model of the chip and its PSRAM, and draws the
display's frames on the board. Play with the keyboard (arrows, F fire, Space use, comma/period
strafe, M menu, Enter) or a gamepad (`input.js` maps a standard controller).

## Why it runs Doom

The Pico Plus 2's 8 MB of PSRAM is mapped at 0x1100_0000 through the XIP cache, so Doom runs as an
ordinary program: the zone heap and the screens in PSRAM, the full DOOM1.WAD in flash, on one
Hazard3 core at 150 MHz. The display takes each 320 × 200 frame as RGB565 over SPI0 at 25 MHz.

## Power

Two 18650 Li-ion cells in Keystone 1042 holders on the back, in parallel (1S2P, 3.0–4.2 V), the same
power section as `doom/rp2350-handheld`:

- **Reverse cells:** an AO3401A P-MOSFET in the plus line, its gate at the cells' minus: cells put
  in backwards leave it off and the board unpowered (it conducts both ways when they are right, so
  charging goes through it too). One cell reversed against the other is what the **per-cell fuses**
  are for: each holder's + reaches the pack through its own 2 A resettable fuse (Littelfuse
  1812L200/16GR: 16 V, 100 A interrupting), so a cell put in backwards, or one much fuller than
  the other, trips both in milliseconds instead of shorting the two cells together (tens of
  amperes); take the cell out and they reset. Still put each cell's + at the end the silkscreen
  marks.
- **Protection:** DW01A + FS8205A in the pack's minus: over-charge 4.3 V, over-discharge 2.4 V,
  over-current about 3 A and short circuit, for the pack. Flat-top unprotected 18650 cells fit the
  holders.
- **Charger with power path:** a TI BQ24075 from the module's VBUS, in USB500 mode (at most 500 mA
  from the port), 800 mA fast charge (RISET 1.13 kΩ), input limit set by RILIM 1.18 kΩ, safety
  timers off (two cells in parallel charge longer than its longest timer; termination is by
  current), TS tied to 10 kΩ (no thermistor). Its output SYS runs the board from USB when one is
  plugged in and from the cells otherwise; SYS reaches the module's VSYS through a 1N5819HW
  Schottky, beside the module's own VBUS diode.
- **On/off:** the slide switch on the left edge pulls the module's 3V3_EN low (its buck-boost off;
  the charger still charges with the switch off).

| State | Current at 3.3 V (estimate) |
|---|---|
| RP2350 at 150 MHz + PSRAM | ~40 mA |
| ILI9341 2.8" with backlight | ~60–80 mA |
| PCM5102A | ~20 mA |
| **Total** | **~130 mA at 3.3 V ≈ 0.5 W with losses → ~130 mA from 3.7 V** |

Two 3000 mAh cells → **about 45 h** of play (estimate). A full charge of two empty cells at 800 mA
takes about 8 h (longer from a USB 2.0 port, which the charger limits to 500 mA).

## Charging

Plug a USB charger or computer into the module's USB. The red LED (CHG) is on while the cells
charge and goes out when they are full; the green LED (USB) is on while USB power is present. The
board runs from USB while it charges, switched on or off. Insert the cells with + at the end the
back's silkscreen marks.

## Modules plugged in by hand

The assembly solders two 1x20 female sockets and one 1x14 female socket; the modules are bought
separately and plugged in:

- **U1: Pimoroni Pico Plus 2** (PIM724, with headers): on the back, components facing the board, the USB end
  at the top edge.
- **DS1: 2.8" ILI9341 SPI TFT with touch, MSP2807** (14 pins), on the front.

## Firmware: build and flash

- `doom/` is the program: `doom_rp2350.c` is the platform layer (clocks, the PSRAM, the display on
  SPI0, the buttons, the timer), the engine is sysprog21/doom_riscv, unchanged. Pins: display SCK
  GP18, MOSI GP19, CS GP17, D/C GP20, RESET GP21, backlight GP22, the touch's CS GP13 held high;
  buttons GP0 … GP9 (up, down, left, right, fire, use, strafe left, strafe right, menu, enter).
  No console (GP0 and GP1 are buttons) and no sound yet (the DAC stays silent).
- **Build:** in PCBKit, the Laboratory's **Run** builds it (RISC-V, `DOOM1.WAD` linked into flash);
  then export the firmware (`export.run { format: "firmware" }`, or the app's export menu): `U1.uf2`.
- **Flashing on arrival:** hold the module's BOOTSEL button and plug its USB into a computer: it
  appears as the RP2350 drive; copy `U1.uf2` onto it and it reboots into the game; or
  `picotool load -x U1.uf2`. Nothing on the board to configure.

## Bill of materials

Rough cost at 10 pieces (estimates): Pimoroni Pico Plus 2 $13 · 2 × 20-pin sockets
$0.50 · ILI9341 2.8" touch module $7.00 · PCM5102A $2.00 · jack $0.60 · 10 buttons $2.90 · charger,
protection and passives $2.00 · two 18650 holders $9.80 · PCB $2.00 → **about $40** without the cells.

<!-- BOM -->
The assembly BOM as `pcbkit export --format fab` writes it (JLCPCB assembly: LCSC codes; the modules' lines are their sockets):

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
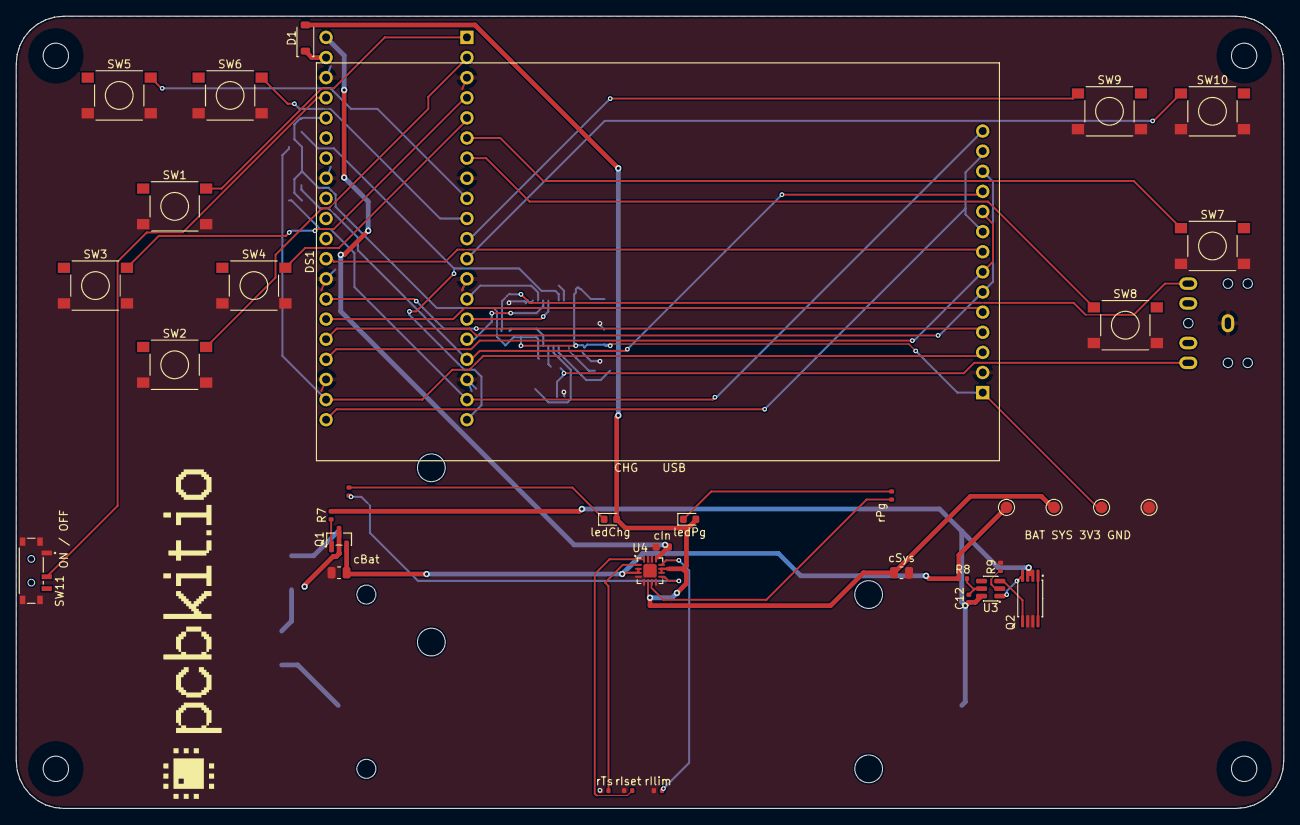
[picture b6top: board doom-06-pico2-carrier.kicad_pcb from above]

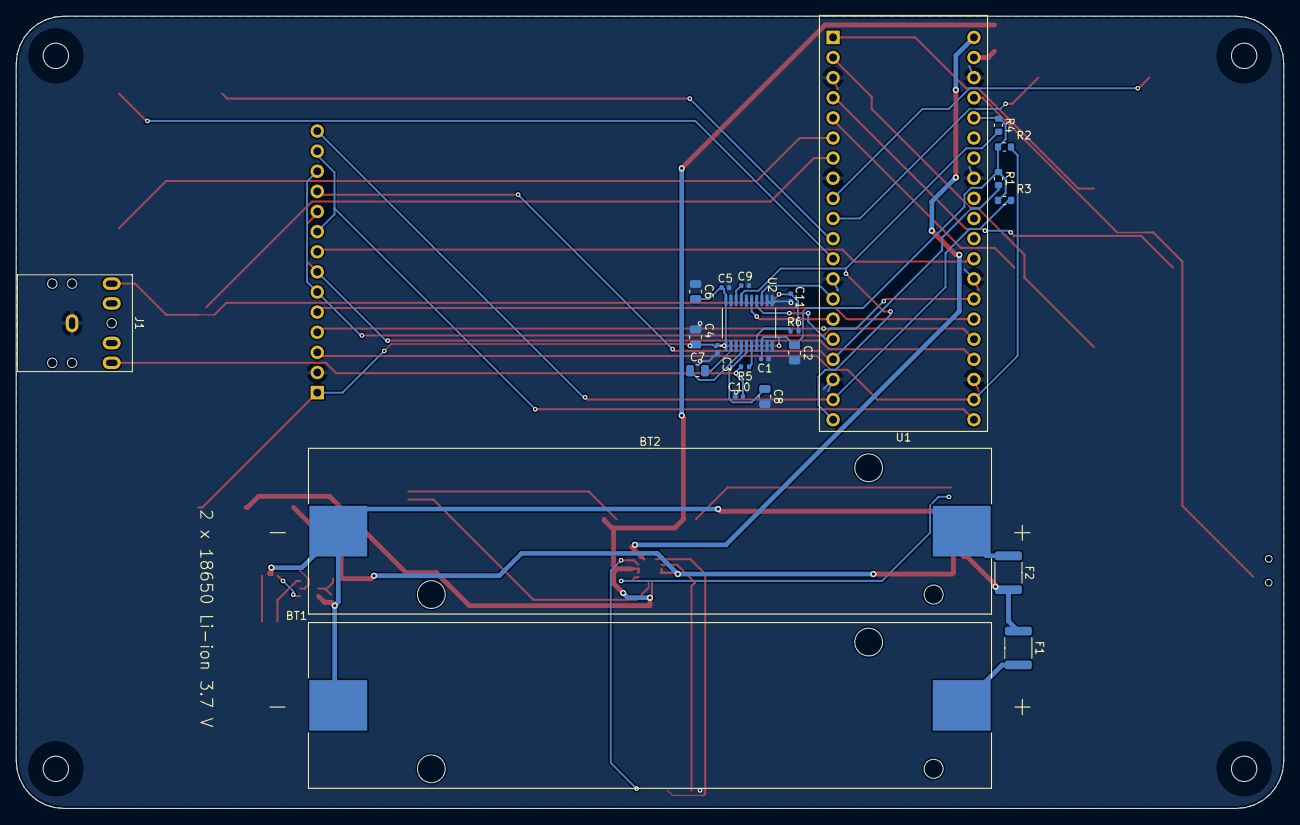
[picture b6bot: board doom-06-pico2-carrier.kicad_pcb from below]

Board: 2 copper layers, 160.0 x 100.0 mm, 64 parts (24 on the bottom side), 55 nets.

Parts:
BT1, BT2: 1042; BatteryHolder_Keystone_1042_1x18650
C1, C3, C5, C9, C12: 100nF; C_0402_1005Metric
C2, C4, C6: 10uF; C_0805_2012Metric
C7, C8: 2.2uF; C_0805_2012Metric
C10, C11: 2.2nF; C_0402_1005Metric
D1: 1N5819HW-7-F; D_SOD-123
DS1: MSP2807 2.8in 240x320 SPI TFT module with touch (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; TFT_2.8in_ILI9341_Socket_1x14_P2.54mm
F1, F2: PTC 2000mA; Fuse_1812_4532Metric
H1, H2, H3, H4: MountingHole_3.2mm_M3
J1: SJ1-3525N; Jack_3.5mm_SameSky_SJ1-352XN_Horizontal
Q1: AO3401A; SOT-23
Q2: FS8205A; TSSOP-8_4.4x2.93mm_P0.65mm
R1, R2, R3, R4: 10kohm; R_0603_1608Metric
R5, R6: 470ohm; R_0402_1005Metric
R7: 100kohm; R_0402_1005Metric
R8: 100ohm; R_0402_1005Metric
R9: 1kohm; R_0402_1005Metric
SW1, SW2, SW3, SW4, SW5, SW6, SW7, SW8, SW9, SW10: PTS645SM43SMTR92 LFS; SW_Tactile_SPST_6x6mm_SMD
SW11: MSK12C02; SW_Slide_SPDT_Shouhan_MSK12C02
U1: PIM724; Pimoroni_Pico_Plus_2_Socket_2x20_P2.54mm_W17.78mm
U2: PCM5102APWR; TSSOP-20_4.4x6.5mm_P0.65mm
U3: DW01A; SOT-6_1.6x2.9mm_P0.95mm
U4: BQ24075RGTR; QFN-16-1EP_3x3mm_P0.5mm_EP1.68x1.68mm
cBat: 4.7uF; C_0805_2012Metric
cIn: 1uF; C_0603_1608Metric
cSys: 4.7uF; C_0805_2012Metric
ledChg: red; LED_0603_1608Metric
ledPg: green; LED_0603_1608Metric
logo: Logo_PCBKit_pcbkit.io
rChg: 1.5kohm; R_0402_1005Metric
rIlim: 1.18kohm; R_0402_1005Metric
rIset: 1.13kohm; R_0402_1005Metric
rPg: 1.5kohm; R_0402_1005Metric
rTs: 10kohm; R_0402_1005Metric
tpBat: TestPoint_Round_D1.5mm
tpGnd: TestPoint_Round_D1.5mm
tpSys: TestPoint_Round_D1.5mm
tpV3: TestPoint_Round_D1.5mm

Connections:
BAT: Q1.2 (S), R8.1 (a), U4.2 (BAT), U4.3 (BAT), cBat.1 (a), tpBat.1
BAT_IN: F1.2 (b), F2.2 (b), Q1.3 (D)
CELL1_P: BT1.2 (C2), F1.1 (a)
CELL2_P: BT2.2 (C2), F2.1 (a)
CELL_N: BT1.1 (C1), BT2.1 (C1), C12.1 (a), Q2.2 (S1), Q2.3 (S1), R7.1 (a), U3.6 (GND)
CHG_LED: ledChg.1 (K), rChg.2 (b)
CHG_N: U4.9 (nCHG), rChg.1 (a)
DAC_LDO: C9.1 (a), U2.18 (LDOO)
DAC_MUTE: R4.2 (b), U1.20 (GP15), U2.17 (XSMT)
DAC_VNEG: C8.1 (a), U2.5 (VNEG)
DOWN: SW2.1 (a), U1.2 (GP1)
ENTER: SW10.1 (a), U1.12 (GP9)
FIRE: SW7.1 (a), U1.6 (GP4)
GND: C1.2 (b), C2.2 (b), C3.2 (b), C4.2 (b), C5.2 (b), C6.2 (b), C8.2 (b), C9.2 (b), C10.2 (b), C11.2 (b), DS1.2 (GND), J1.1 (SLEEVE), Q2.6 (S2), Q2.7 (S2), R9.2 (b), SW1.2 (b), SW2.2 (b), SW3.2 (b), SW4.2 (b), SW5.2 (b), SW6.2 (b), SW7.2 (b), SW8.2 (b), SW9.2 (b), SW10.2 (b), SW11.1 (A), SW11.4 (SHELL), U1.3 (GND), U1.8 (GND), U1.13 (GND), U1.18 (GND), U1.23 (GND), U1.28 (GND), U1.33 (AGND), U1.38 (GND), U2.3 (CPGND), U2.9 (AGND), U2.10 (DEMP), U2.11 (FLT), U2.12 (SCK), U2.16 (FMT), U2.19 (DGND), U4.4 (nCE), U4.5 (EN2), U4.8 (VSS), U4.14 (TMR), U4.15 (SYSOFF), U4.17 (VSS), cBat.2 (b), cIn.2 (b), cSys.2 (b), rIlim.2 (b), rIset.2 (b), rTs.2 (b), tpGnd.1
I2S_BCK: U1.14 (GP10), U2.13 (BCK)
I2S_DIN: U1.16 (GP12), U2.14 (DIN)
I2S_LRCK: U1.15 (GP11), U2.15 (LRCK)
ILIM: U4.12 (ILIM), rIlim.1 (a)
ISET: U4.16 (ISET), rIset.1 (a)
LCD_BL: DS1.8 (LED), U1.29 (GP22)
LCD_CS: DS1.3 (CS), R2.1 (a), U1.22 (GP17)
LCD_DC: DS1.5 (DC), U1.26 (GP20)
LCD_RST: DS1.4 (RESET), U1.27 (GP21)
LEFT: SW3.1 (a), U1.4 (GP2)
LINE_L: C10.1 (a), J1.2 (TIP), R5.2 (b)
LINE_R: C11.1 (a), J1.3 (RING), R6.2 (b)
MENU: SW9.1 (a), U1.11 (GP8)
MISO: DS1.9 (SDO), DS1.13 (T_DO), U1.21 (GP16)
MOSI: DS1.6 (SDI), DS1.12 (T_DIN), U1.25 (GP19)
unnamed: C7.1 (a), U2.2 (CAPP)
unnamed: C7.2 (b), U2.4 (CAPM)
unnamed: C12.2 (b), R8.2 (b), U3.5 (VCC)
unnamed: Q2.4 (G1), U3.1 (OD)
unnamed: Q2.5 (G2), U3.3 (OC)
unnamed: R5.1 (a), U2.6 (OUTL)
unnamed: R6.1 (a), U2.7 (OUTR)
unnamed: R9.1 (a), U3.2 (CS)
PG_LED: ledPg.1 (K), rPg.1 (a)
PG_N: U4.7 (nPGOOD), rPg.2 (b)
PWR_EN: SW11.2 (COM), U1.37 (P3V3_EN)
RIGHT: SW4.1 (a), U1.5 (GP3)
SCK: DS1.7 (SCK), DS1.10 (T_CLK), U1.24 (GP18)
STRAFE_L: SW5.1 (a), U1.9 (GP6)
STRAFE_R: SW6.1 (a), U1.10 (GP7)
SYS: D1.2 (A), U4.6 (EN1), U4.10 (OUT), U4.11 (OUT), cSys.1 (a), ledChg.2 (A), ledPg.2 (A), tpSys.1
TS: U4.1 (TS), rTs.1 (a)
T_CS: DS1.11 (T_CS), R1.2 (b), U1.17 (GP13)
T_IRQ: DS1.14 (T_IRQ), R3.1 (a), U1.19 (GP14)
U3Support/DRAIN: Q2.1 (D12), Q2.8 (D12)
UP: SW1.1 (a), U1.1 (GP0)
USE: SW8.1 (a), U1.7 (GP5)
V3: C1.1 (a), C2.1 (a), C3.1 (a), C4.1 (a), C5.1 (a), C6.1 (a), DS1.1 (VCC), R1.1 (a), R2.2 (b), R3.2 (b), R4.1 (a), U1.36 (P3V3), U2.1 (CPVDD), U2.8 (AVDD), U2.20 (DVDD), tpV3.1
VBUS: U1.40 (VBUS), U4.13 (IN), cIn.1 (a)
VSYS: D1.1 (K), U1.39 (VSYS)
reversed/gate: Q1.1 (G), R7.2 (b)
